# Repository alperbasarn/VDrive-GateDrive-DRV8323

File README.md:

# VDrive-GateDrive-DRV8323
Gate drive stage with DRV8323 from TI

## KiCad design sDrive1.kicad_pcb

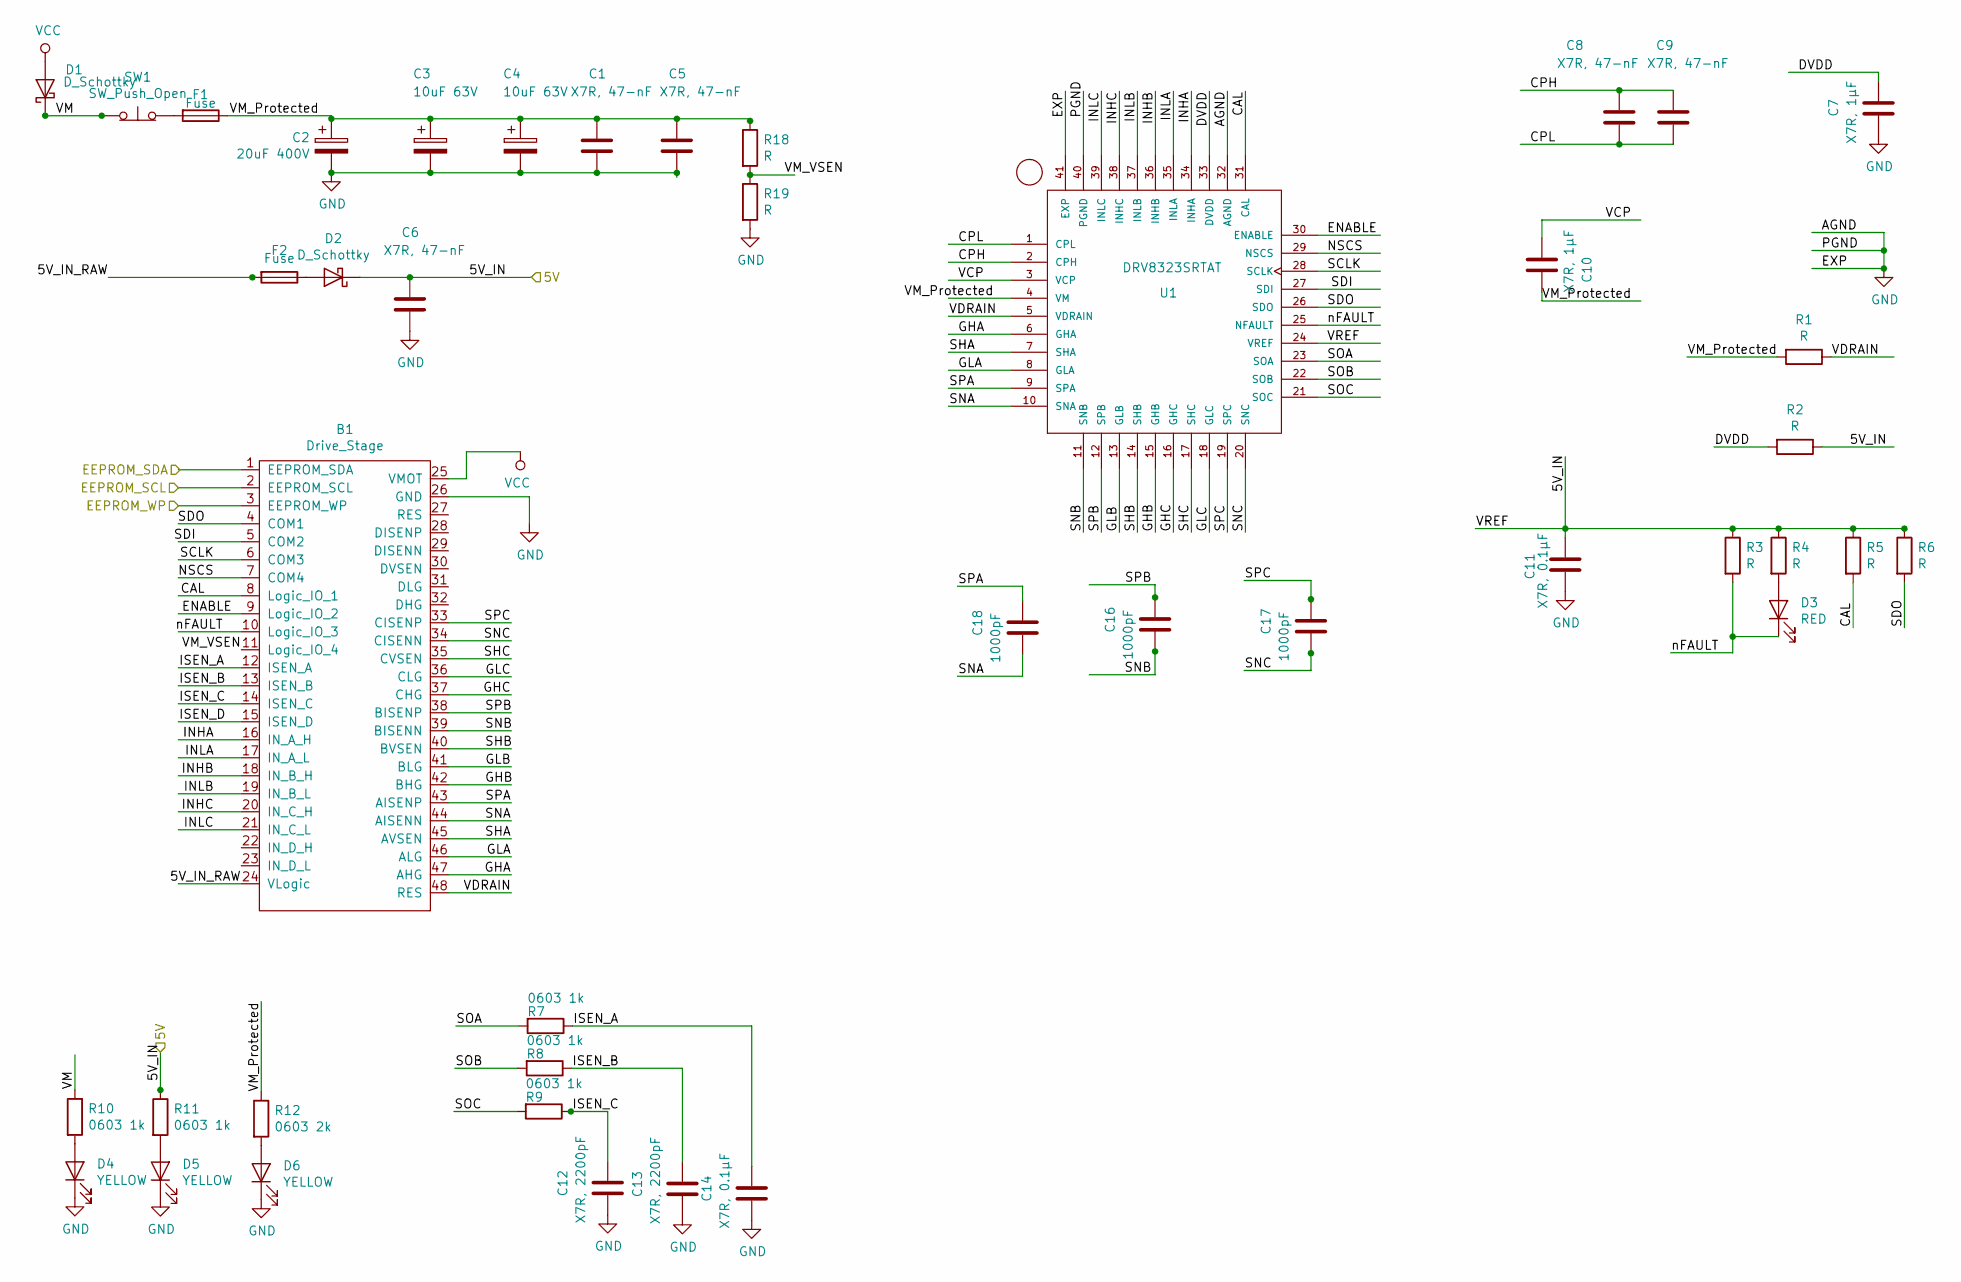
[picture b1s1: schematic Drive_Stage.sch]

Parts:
B1: Drive_Stage; stage2
C1, C5, C6: X7R, 47-nF; C_0603_1608Metric_Pad1.05x0.95mm_HandSolder
C2: 20uF 400V; CP_Elec_4x5.3
C3, C4: 10uF 63V; CP_Elec_4x5.3
C7, C10: X7R, 1µF; C_0805_2012Metric_Pad1.15x1.40mm_HandSolder
C8, C9: X7R, 47-nF; C_0805_2012Metric_Pad1.15x1.40mm_HandSolder
C11: X7R, 0.1µF; C_0805_2012Metric_Pad1.15x1.40mm_HandSolder
C12, C13: X7R, 2200pF; C_0603_1608Metric_Pad1.05x0.95mm_HandSolder
C14: X7R, 0.1µF; C_0603_1608Metric_Pad1.05x0.95mm_HandSolder
C16, C17, C18: 1000pF; C_0603_1608Metric_Pad1.05x0.95mm_HandSolder
D1, D2: D_Schottky; D_0603_1608Metric_Pad1.05x0.95mm_HandSolder
D3: RED; LED_0603_1608Metric_Pad1.05x0.95mm_HandSolder
D4, D5, D6: YELLOW; LED_0603_1608Metric_Pad1.05x0.95mm_HandSolder
F1: Fuse; Fuse_0805_2012Metric_Pad1.15x1.40mm_HandSolder
F2: Fuse; Fuse_0603_1608Metric_Pad1.05x0.95mm_HandSolder
R1, R2, R3, R4, R5, R6, R18, R19: R; R_0603_1608Metric_Pad1.05x0.95mm_HandSolder
R7, R8, R9, R10, R11: 0603 1k; R_0603_1608Metric_Pad1.05x0.95mm_HandSolder
R12: 0603 2k; R_0603_1608Metric_Pad1.05x0.95mm_HandSolder
SW1: SW_Push_Open; SW_DIP_SPSTx01_Slide_6.7x4.1mm_W6.73mm_P2.54mm_LowProfile_J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
U1: DRV8323SRTAT; QFN50P600X600X80-41N415X415

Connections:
/Drive_Stage/5V: C6.1, C11.1, D2.1 (K), R2.1, R3.1, R4.1, R5.1, R6.1, R11.1, U1.24 (VREF); also elsewhere on the board
/Drive_Stage/5V_IN_RAW: B1.24 (VLogic), F2.2
/Drive_Stage/CAL: B1.8 (Logic_IO_1), R5.2, U1.31 (CAL)
/Drive_Stage/CPH: C8.1, C9.1, U1.2 (CPH)
/Drive_Stage/CPL: C8.2, C9.2, U1.1 (CPL)
/Drive_Stage/DVDD: C7.1, R2.2, U1.33 (DVDD)
/Drive_Stage/EEPROM_SCL: B1.2 (EEPROM_SCL); also elsewhere on the board
/Drive_Stage/EEPROM_SDA: B1.1 (EEPROM_SDA); also elsewhere on the board
/Drive_Stage/EEPROM_WP: B1.3 (EEPROM_WP); also elsewhere on the board
/Drive_Stage/ENABLE: B1.9 (Logic_IO_2), U1.30 (ENABLE)
/Drive_Stage/GHA: B1.47 (AHG), U1.6 (GHA)
/Drive_Stage/GHB: B1.42 (BHG), U1.15 (GHB)
/Drive_Stage/GHC: B1.37 (CHG), U1.16 (GHC)
/Drive_Stage/GLA: B1.46 (ALG), U1.8 (GLA)
/Drive_Stage/GLB: B1.41 (BLG), U1.13 (GLB)
/Drive_Stage/GLC: B1.36 (CLG), U1.18 (GLC)
/Drive_Stage/INHA: B1.16 (IN_A_H), U1.34 (INHA)
/Drive_Stage/INHB: B1.18 (IN_B_H), U1.36 (INHB)
/Drive_Stage/INHC: B1.20 (IN_C_H), U1.38 (INHC)
/Drive_Stage/INLA: B1.17 (IN_A_L), U1.35 (INLA)
/Drive_Stage/INLB: B1.19 (IN_B_L), U1.37 (INLB)
/Drive_Stage/INLC: B1.21 (IN_C_L), U1.39 (INLC)
/Drive_Stage/ISEN_A: B1.12 (ISEN_A), C14.1, R7.1
/Drive_Stage/ISEN_B: B1.13 (ISEN_B), C13.1, R8.1
/Drive_Stage/ISEN_C: B1.14 (ISEN_C), C12.1, R9.1
/Drive_Stage/ISEN_D: B1.15 (ISEN_D)
/Drive_Stage/NSCS: B1.7 (COM4), U1.29 (NSCS)
/Drive_Stage/SCLK: B1.6 (COM3), U1.28 (SCLK)
/Drive_Stage/SDI: B1.5 (COM2), U1.27 (SDI)
/Drive_Stage/SDO: B1.4 (COM1), R6.2, U1.26 (SDO)
/Drive_Stage/SHA: B1.45 (AVSEN), U1.7 (SHA)
/Drive_Stage/SHB: B1.40 (BVSEN), U1.14 (SHB)
/Drive_Stage/SHC: B1.35 (CVSEN), U1.17 (SHC)
/Drive_Stage/SNA: B1.44 (AISENN), C18.2, U1.10 (SNA)
/Drive_Stage/SNB: B1.39 (BISENN), C16.2, U1.11 (SNB)
/Drive_Stage/SNC: B1.34 (CISENN), C17.2, U1.20 (SNC)
/Drive_Stage/SOA: R7.2, U1.23 (SOA)
/Drive_Stage/SOB: R8.2, U1.22 (SOB)
/Drive_Stage/SOC: R9.2, U1.21 (SOC)
/Drive_Stage/SPA: B1.43 (AISENP), C18.1, U1.9 (SPA)
/Drive_Stage/SPB: B1.38 (BISENP), C16.1, U1.12 (SPB)
/Drive_Stage/SPC: B1.33 (CISENP), C17.1, U1.19 (SPC)
/Drive_Stage/VCP: C10.2, U1.3 (VCP)
/Drive_Stage/VDRAIN: B1.48 (RES), R1.1, U1.5 (VDRAIN)
/Drive_Stage/VM: D1.1 (K), R10.1, SW1.1 (A)
/Drive_Stage/VM_Protected: C1.1, C2.1, C3.1, C4.1, C5.1, C10.1, F1.1, R1.2, R12.1, R18.1, U1.4 (VM)
/Drive_Stage/VM_VSEN: B1.11 (Logic_IO_4), R18.2, R19.1
/Drive_Stage/nFAULT: B1.10 (Logic_IO_3), D3.1 (K), R3.2, U1.25 (NFAULT)
GND: B1.26 (GND), C1.2, C2.2, C3.2, C4.2, C5.2, C6.2, C7.2, C11.2, C12.2, C13.2, C14.2, D4.1 (K), D5.1 (K), D6.1 (K), R19.2, U1.32 (AGND), U1.40 (PGND), U1.41 (EXP); also elsewhere on the board
unnamed: D2.2 (A), F2.1
unnamed: D3.2 (A), R4.2
unnamed: D4.2 (A), R10.2
unnamed: D5.2 (A), R11.2
unnamed: D6.2 (A), R12.2
unnamed: F1.2, SW1.2 (B)
VCC: B1.25 (VMOT), D1.2 (A)

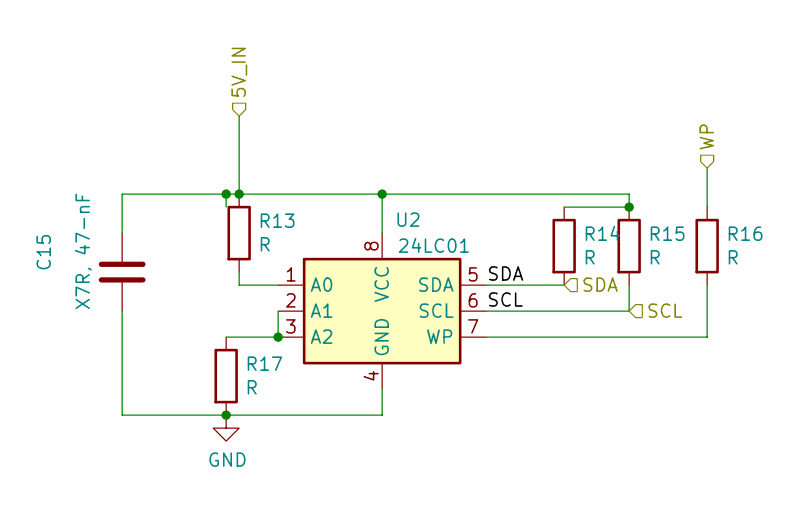
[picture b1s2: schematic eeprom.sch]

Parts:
C15: X7R, 47-nF; C_0603_1608Metric_Pad1.05x0.95mm_HandSolder
R13, R14, R15, R16, R17: R; R_0603_1608Metric_Pad1.05x0.95mm_HandSolder
U2: 24LC01; DFN-8-1EP_3x2mm_P0.5mm_EP1.36x1.46mm

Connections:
/Drive_Stage/5V: C15.1, R13.1, R14.1, R15.1, U2.8 (VCC); also elsewhere on the board
/Drive_Stage/EEPROM_SCL: R15.2, U2.6 (SCL); also elsewhere on the board
/Drive_Stage/EEPROM_SDA: R14.2, U2.5 (SDA); also elsewhere on the board
/Drive_Stage/EEPROM_WP: R16.1; also elsewhere on the board
GND: C15.2, R17.2, U2.4 (GND); also elsewhere on the board
unnamed: R13.2, U2.1 (A0)
unnamed: R16.2, U2.7 (WP)
unnamed: R17.1, U2.2 (A1), U2.3 (A2)

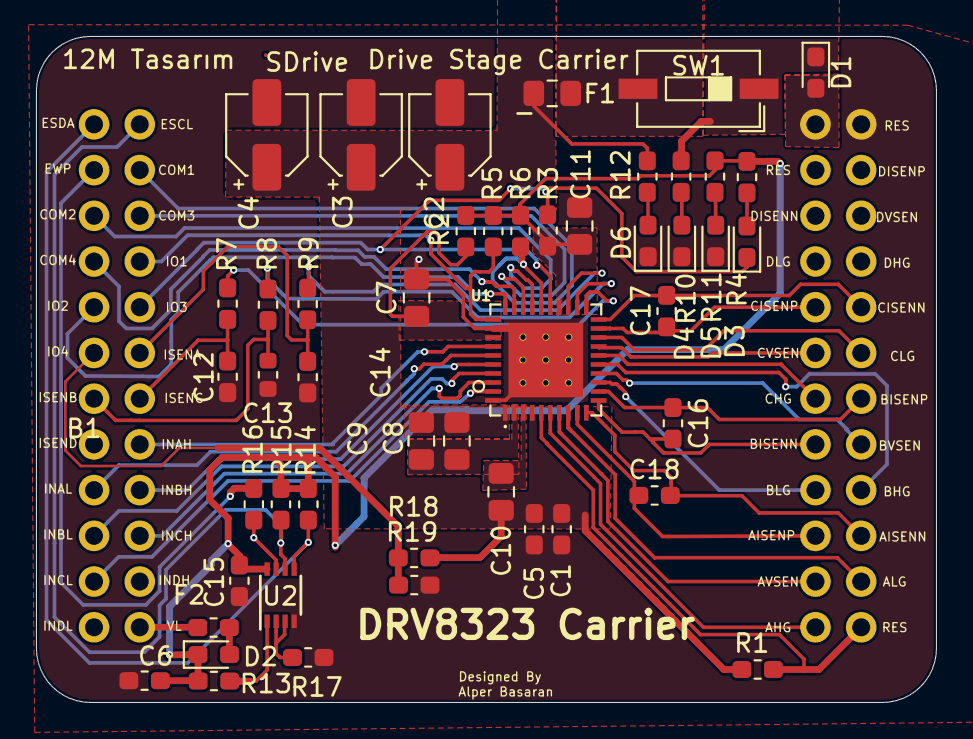
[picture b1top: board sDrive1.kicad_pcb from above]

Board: 2 copper layers, 50.0 x 37.0 mm, 49 parts (0 on the bottom side), 58 nets.

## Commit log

2021-07-17 create repo with current files
2021-07-18 create seperate hierarchical sheet for eeprom
2021-07-18 update pcb layout
    set board cutout
    update eeprom footporint
2021-07-18 add production files
2021-07-21 add voltage supply sense resistors
2021-07-21 update production files
2021-07-29 move VMsen to pin 8
